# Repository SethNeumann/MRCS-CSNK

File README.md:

# REPO NAME: MRCS-CSNK
## License: Creative Commons Attribution-NonCommercial-ShareAlike

The CSNK Version 2 plugs into a cpNode, IOX16 or IOX32 and provides 16 high voltage/current outputs using the ULN2803 chip.  Loads of up to 48 Volts and 0.5A may 
handled (but not all 16 at once!).  Internal clamp diodes are provided for inductive loads (see application note).  Outputs are 0.100" centers and headers and screw
terminals are available.  The CSNK is ideal for situations where you need to drive high current devices (incandescent lamps) and inductive loads.  CSNK offers
compatibility with existing signaling systems or CTC Console using 12-48VDC power for signals.

If you need to drive more than 0.5A, check out our Sounder Driver which can handle up to 10A (momentary) and provides a clamping diode.

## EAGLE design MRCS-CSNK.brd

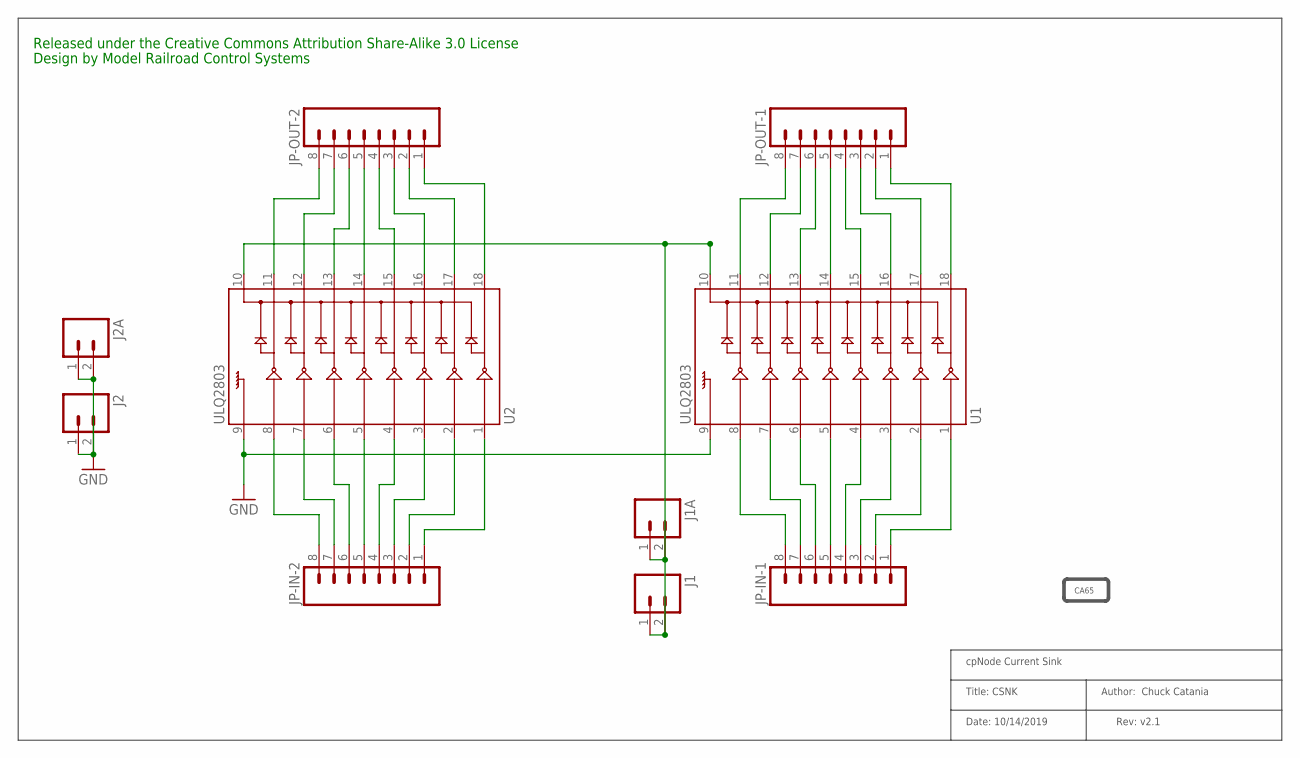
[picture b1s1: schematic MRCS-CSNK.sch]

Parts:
J1, J2: CONNECTOR-M021X02-LOCK; 1X02_LOCK
J1A, J2A: CONNECTOR-M023.5MM-LOCK; SCREWTERMINAL-3.5MM-2_LOCK
JP-IN-1, JP-IN-2: CONNECTOR-M08LOCK; 1X08_LOCK
JP-OUT-1, JP-OUT-2: CONNECTOR-M08LOCK; 1X08_LOCK
PROP65: DOC-CA65B; CA-PROP65-BACK
U1, U2: ULQ2803; DIL18

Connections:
GND: J2.1 (A), J2.2 (B), J2A.1 (A), J2A.2 (B), U1.9, U2.9
unnamed: JP-IN-1.1, U1.1
unnamed: JP-IN-1.2, U1.2
unnamed: JP-IN-1.3, U1.3
unnamed: JP-IN-1.4, U1.4
unnamed: JP-IN-1.5, U1.5
unnamed: JP-IN-1.6, U1.6
unnamed: JP-IN-1.7, U1.7
unnamed: JP-IN-1.8, U1.8
unnamed: JP-OUT-1.1, U1.18
unnamed: JP-OUT-1.2, U1.17
unnamed: JP-OUT-1.3, U1.16
unnamed: JP-OUT-1.4, U1.15
unnamed: JP-OUT-1.5, U1.14
unnamed: JP-OUT-1.6, U1.13
unnamed: JP-OUT-1.7, U1.12
unnamed: JP-OUT-1.8, U1.11
unnamed: JP-OUT-2.5, U2.14
unnamed: JP-IN-2.1, U2.1
unnamed: JP-IN-2.2, U2.2
unnamed: JP-IN-2.3, U2.3
unnamed: JP-IN-2.4, U2.4
unnamed: JP-IN-2.5, U2.5
unnamed: JP-IN-2.6, U2.6
unnamed: JP-IN-2.7, U2.7
unnamed: JP-IN-2.8, U2.8
unnamed: JP-OUT-2.8, U2.11
unnamed: JP-OUT-2.7, U2.12
unnamed: JP-OUT-2.6, U2.13
unnamed: JP-OUT-2.4, U2.15
unnamed: JP-OUT-2.3, U2.16
unnamed: JP-OUT-2.2, U2.17
unnamed: JP-OUT-2.1, U2.18
unnamed: J1.1 (A), J1.2 (B), J1A.1 (A), J1A.2 (B), U1.10, U2.10

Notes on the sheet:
Rev: v2.1
Date: 10/14/2019
Title: CSNK
cpNode Current Sink
Author: Chuck Catania
Released under the Creative Commons Attribution Share-Alike 3.0 License
Design by Model Railroad Control Systems

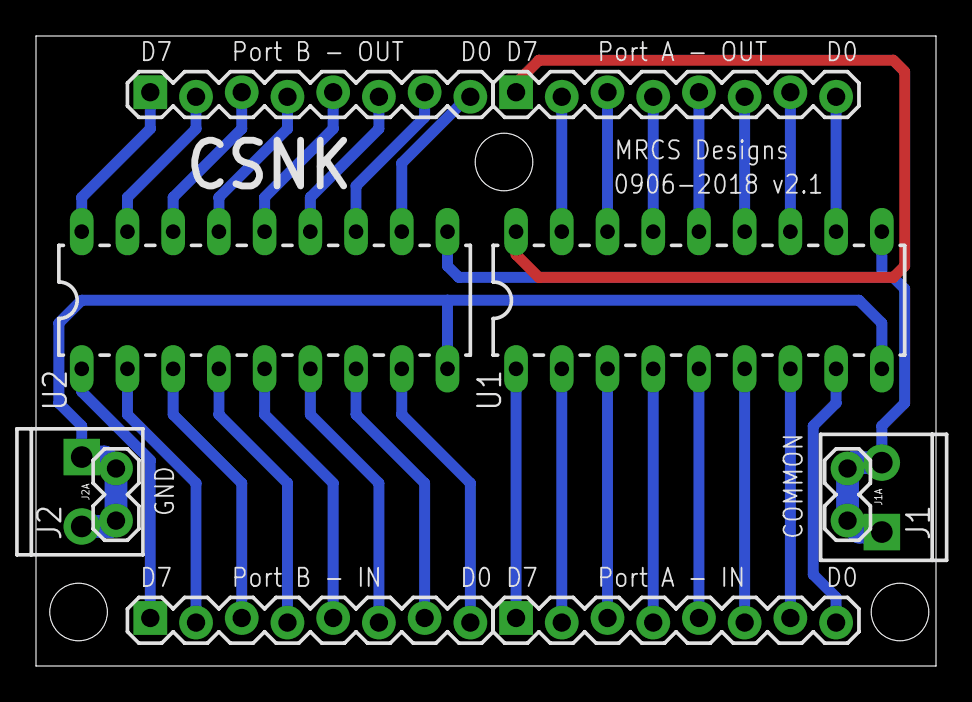
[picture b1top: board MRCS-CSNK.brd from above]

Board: 2 copper layers, 50.0 x 35.0 mm, 11 parts (0 on the bottom side), 34 nets.

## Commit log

2020-12-30 initial commit
    initial commit
2020-12-30 intial commit
    initial commit
2020-12-30 intial commit
    intial commit
2020-12-30 finishing setup
    finishing setup
2020-12-30 moving existing designs into GitHub
    moving existing designs into GitHub
2020-12-30 Create MRCS-CSNK Assembly and Installation Instructions.pdf
    First pass

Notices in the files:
parts and their libraries:
SparkFun-PowerIC: Licensing: Creative Commons ShareAlike 4.0 International - https://creativecommons.org/licenses/by-sa/4.0
